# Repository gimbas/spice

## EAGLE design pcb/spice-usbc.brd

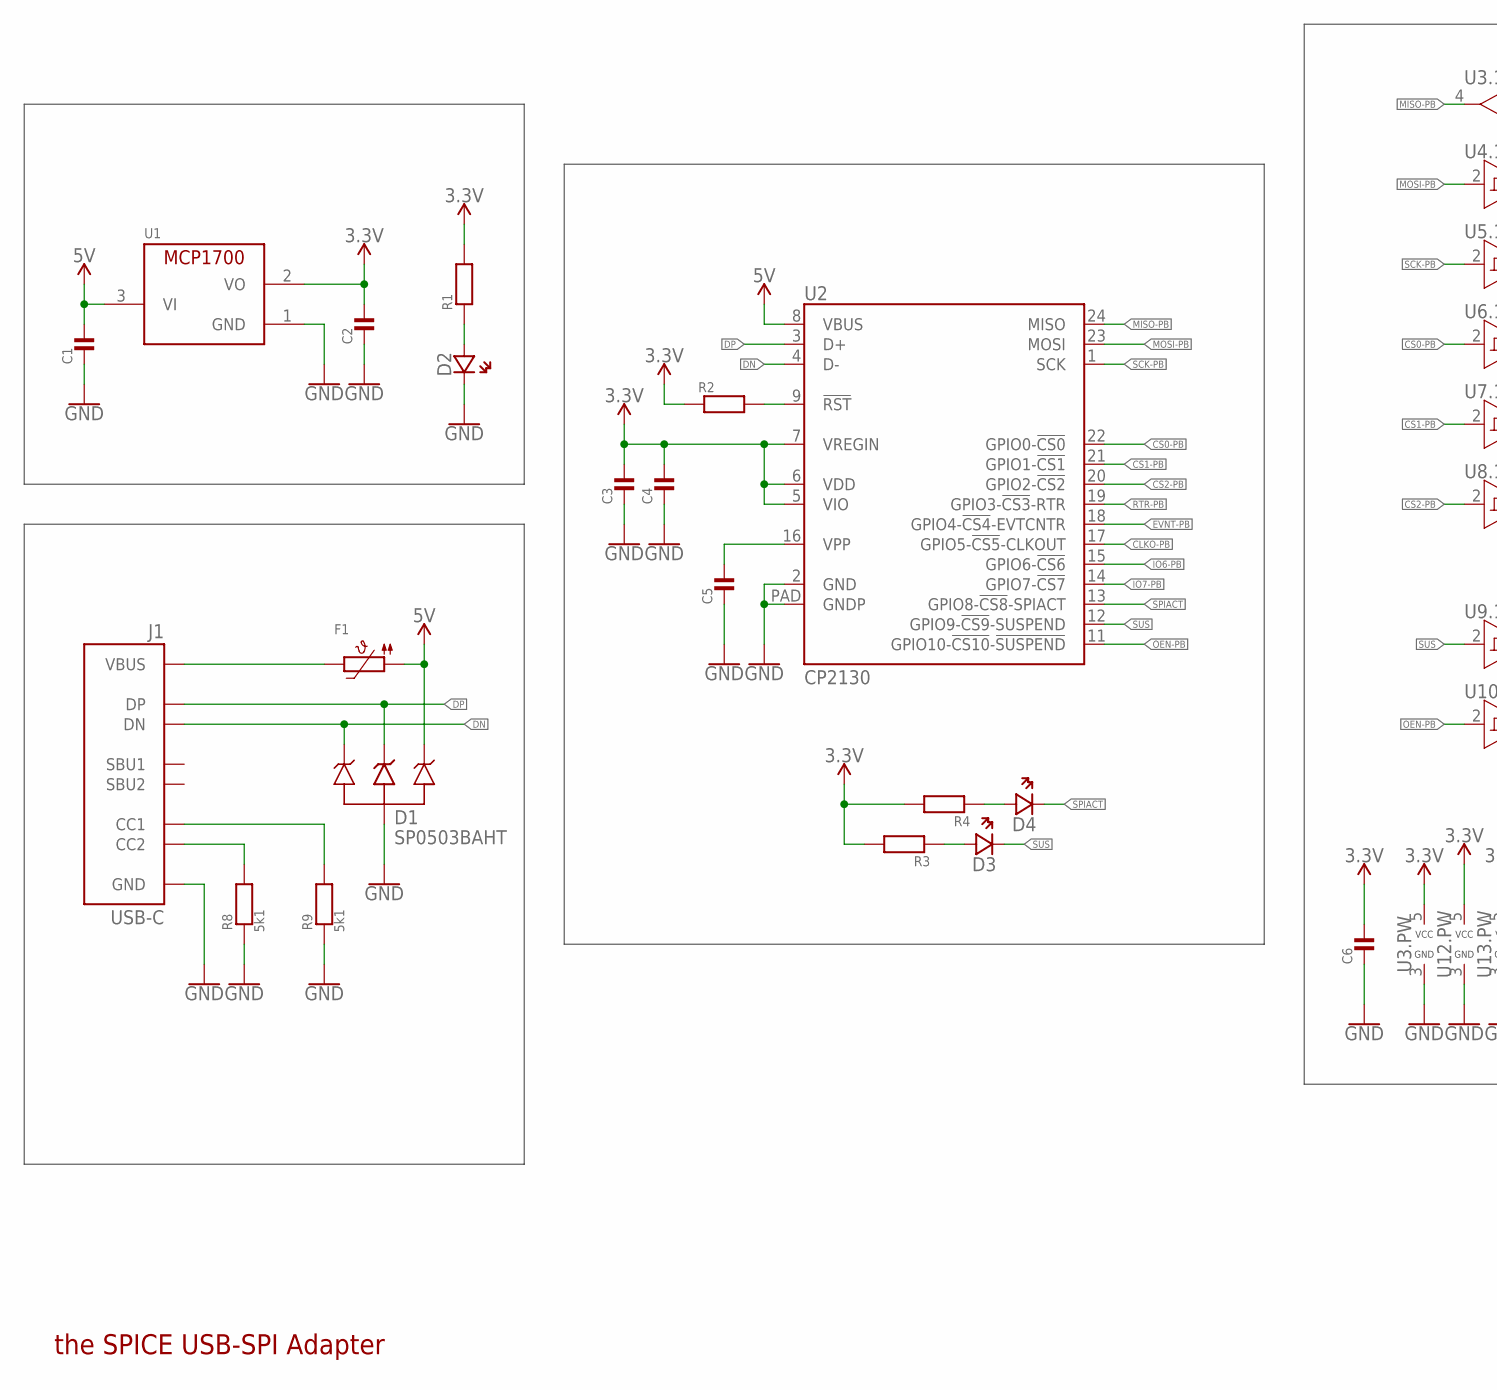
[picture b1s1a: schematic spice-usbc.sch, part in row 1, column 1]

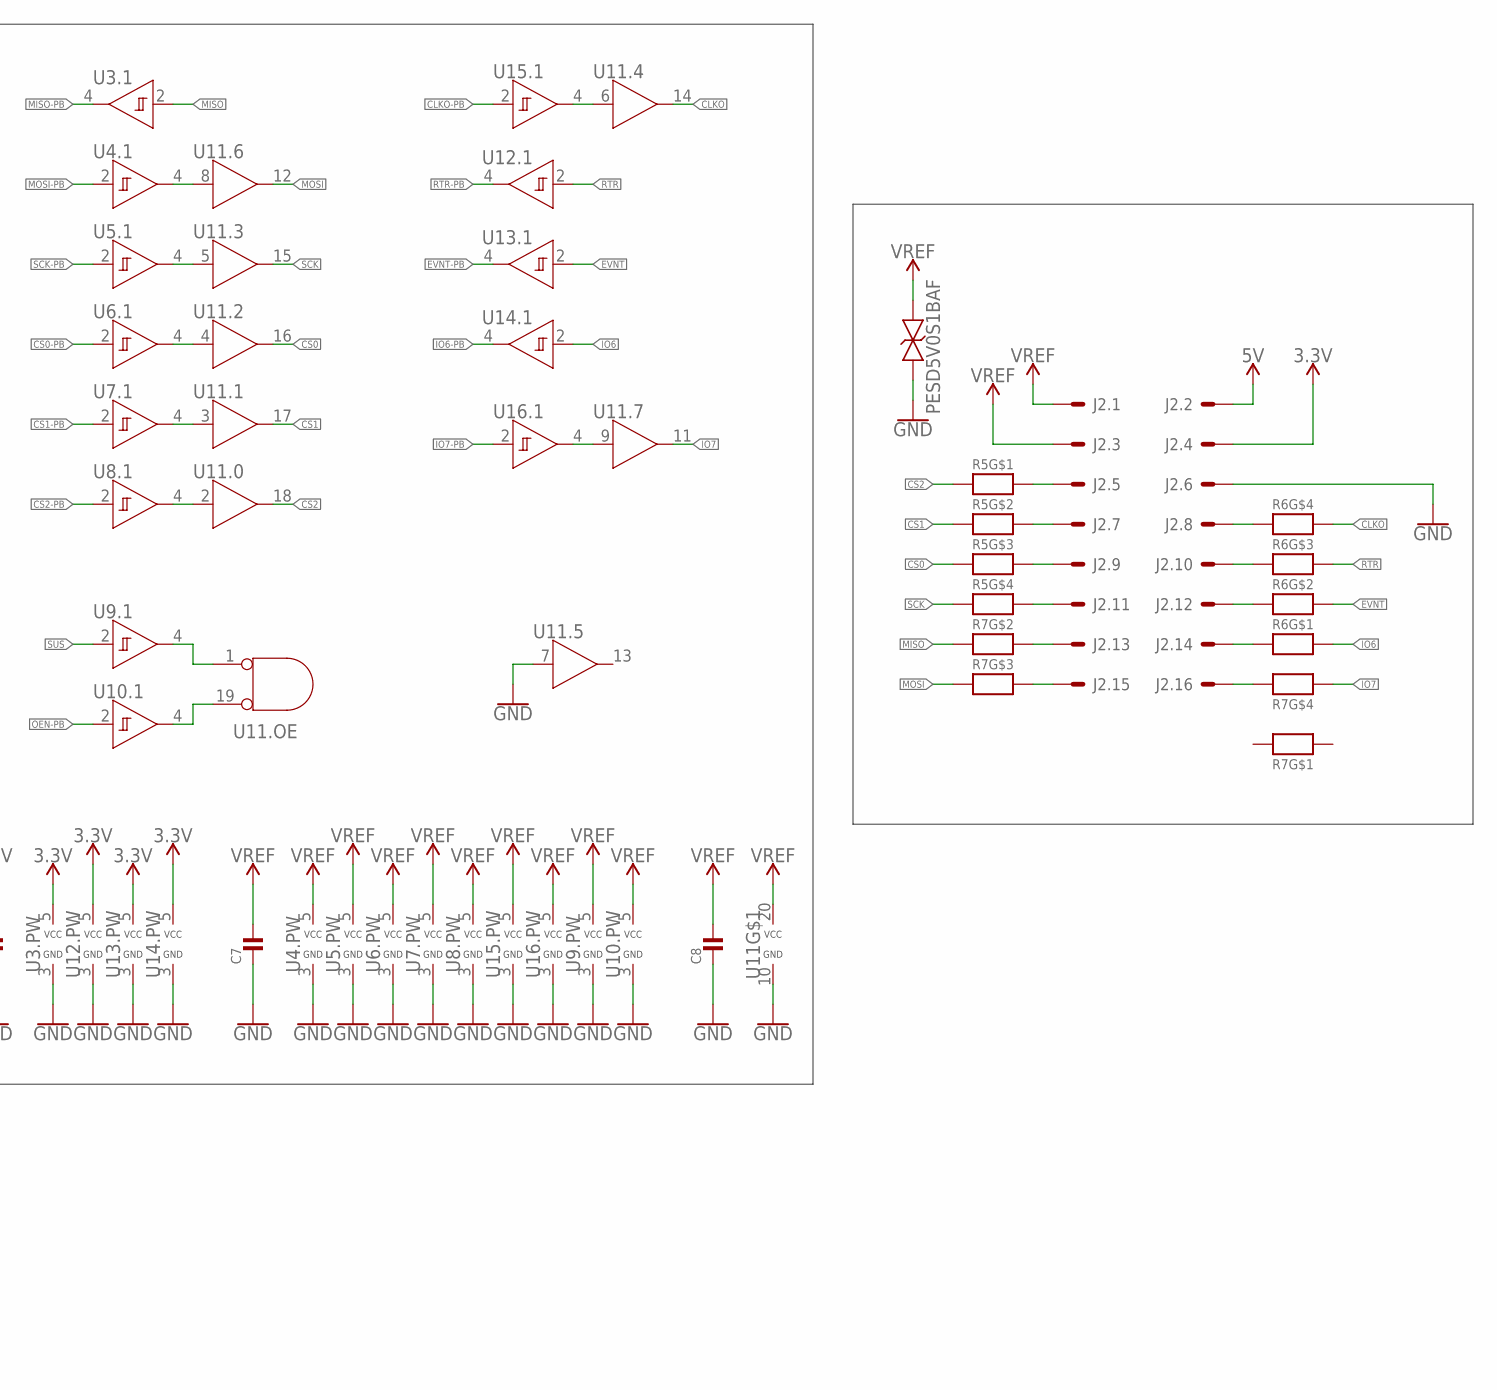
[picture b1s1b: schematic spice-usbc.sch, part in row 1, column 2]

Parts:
C1, C2, C3, C4, C5, C6, C7, C8: MLCC0603; 0603_WAVE
D1: SP0503BAHT; SOT143
D2, D3, D4: LED0603; CHIPLED_0603
D5: PESD5V0S1BAF; SOD323
F1: PTC1210
J1: USB-C
J2: 2X8; 2X8_2.54
R1, R2, R3, R4: RESISTOR0603; 0603_WAVE
R5, R6, R7: RESISTOR_4PACK; RESPACK_4X0603
R8, R9: 5k1; 0603_WAVE
U1: MCP1700T-3302TT; SOT-23
U2: CP2130; QFN24
U3, U4, U5, U6, U7, U8, U9, U10, U12, U13, U14, U15, U16: 74LVC1G17; SC70-5
U11: 74HC541; TSSOP20

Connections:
3.3V: C2.P$1, C3.P$1, C4.P$1, C6.P$1, J2.4, R1.P$2, R2.P$1, R3.P$2, R4.P$2, U1.2 (VO), U2.5 (VIO), U2.6 (VDD), U2.7 (VREGIN), U3.5 (VCC), U12.5 (VCC), U13.5 (VCC), U14.5 (VCC)
5V: C1.P$1, D1.4, F1.P$1 (1), J2.2, U1.3 (VI), U2.8 (VBUS)
CLKO: R6.5 (2), U11.14 (Y)
CLKO-PB: U2.17 (GPIO5-!CS5!-CLKOUT), U15.2 (A)
CS0: R5.3 (1), U11.16 (Y)
CS0-PB: U2.22 (GPIO0-!CS0), U6.2 (A)
CS1: R5.2 (1), U11.17 (Y)
CS1-PB: U2.21 (GPIO1-!CS1), U7.2 (A)
CS2: R5.1, U11.18 (Y)
CS2-PB: U2.20 (GPIO2-!CS2), U8.2 (A)
DN: D1.2, J1.A7 (DN), J1.B7 (DN), U2.4 (D-)
DP: D1.3, J1.A6 (DP), J1.B6 (DP), U2.3 (D+)
EVNT: R6.7 (2), U13.2 (A)
EVNT-PB: U2.18 (GPIO4-!CS4!-EVTCNTR), U13.4 (Y)
GND: C1.P$2, C2.P$2, C3.P$2, C4.P$2, C5.P$2, C6.P$2, C7.P$2, C8.P$2, D1.1, D2.C (CA), D5.P$2, J1.A1_B12 (GND), J1.B1_A12 (GND), J1.SHIELD0 (GND), J1.SHIELD1 (GND), J1.SHIELD2 (GND), J1.SHIELD3 (GND), J2.6, R8.P$1, R9.P$1, U1.1 (GND), U2.2 (GND), U2.PAD (GNDP), U3.3 (GND), U4.3 (GND), U5.3 (GND), U6.3 (GND), U7.3 (GND), U8.3 (GND), U9.3 (GND), U10.3 (GND), U11.7 (A), U11.10 (GND), U12.3 (GND), U13.3 (GND), U14.3 (GND), U15.3 (GND), U16.3 (GND)
IO6: R6.8 (2), U14.2 (A)
IO6-PB: U2.15 (GPIO6-!CS6), U14.4 (Y)
IO7: R7.4 (1), U11.11 (Y)
IO7-PB: U2.14 (GPIO7-!CS7), U16.2 (A)
MISO: R7.2 (1), U3.2 (A)
MISO-PB: U2.24 (MISO), U3.4 (Y)
MOSI: R7.3 (1), U11.12 (Y)
MOSI-PB: U2.23 (MOSI), U4.2 (A)
unnamed: U11.6 (A), U15.4 (Y)
unnamed: D3.A (AN), R3.P$1
unnamed: D4.A (AN), R4.P$1
unnamed: R2.P$2, U2.9 (!RST)
unnamed: U5.4 (Y), U11.5 (A)
unnamed: J2.13, R7.7 (2)
unnamed: U4.4 (Y), U11.8 (A)
unnamed: C5.P$1, U2.16 (VPP)
unnamed: D2.A (AN), R1.P$1
unnamed: U6.4 (Y), U11.4 (A)
unnamed: U7.4 (Y), U11.3 (A)
unnamed: U8.4 (Y), U11.2 (A)
unnamed: F1.P$2 (2), J1.A4_B9 (VBUS), J1.B4_A9 (VBUS)
unnamed: U11.9 (A), U16.4 (Y)
unnamed: J1.B5 (CC2), R8.P$2
unnamed: J2.15, R7.6 (2)
unnamed: J2.5, R5.8 (2)
unnamed: J2.7, R5.7 (2)
unnamed: J2.9, R5.6 (2)
unnamed: J2.11, R5.5 (2)
unnamed: J2.8, R6.4 (1)
unnamed: J2.10, R6.3 (1)
unnamed: J2.12, R6.2 (1)
unnamed: J2.14, R6.1
unnamed: J2.16, R7.5 (2)
unnamed: J1.A5 (CC1), R9.P$2
OE1: U9.4 (Y), U11.1 (A)
OE2: U10.4 (Y), U11.19 (B)
OEN-PB: U2.11 (GPIO10-!CS10!-!SUSPEND), U10.2 (A)
RTR: R6.6 (2), U12.2 (A)
RTR-PB: U2.19 (GPIO3-!CS3!-RTR), U12.4 (Y)
SCK: R5.4 (1), U11.15 (Y)
SCK-PB: U2.1 (SCK), U5.2 (A)
SPIACT: D4.C (CA), U2.13 (GPIO8-!CS8!-SPIACT)
SUS: D3.C (CA), U2.12 (GPIO9-!CS9!-SUSPEND), U9.2 (A)
VREF: C7.P$1, C8.P$1, D5.P$1, J2.1, J2.3, U4.5 (VCC), U5.5 (VCC), U6.5 (VCC), U7.5 (VCC), U8.5 (VCC), U9.5 (VCC), U10.5 (VCC), U11.20 (VCC), U15.5 (VCC), U16.5 (VCC)

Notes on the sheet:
the SPICE USB-SPI Adapter

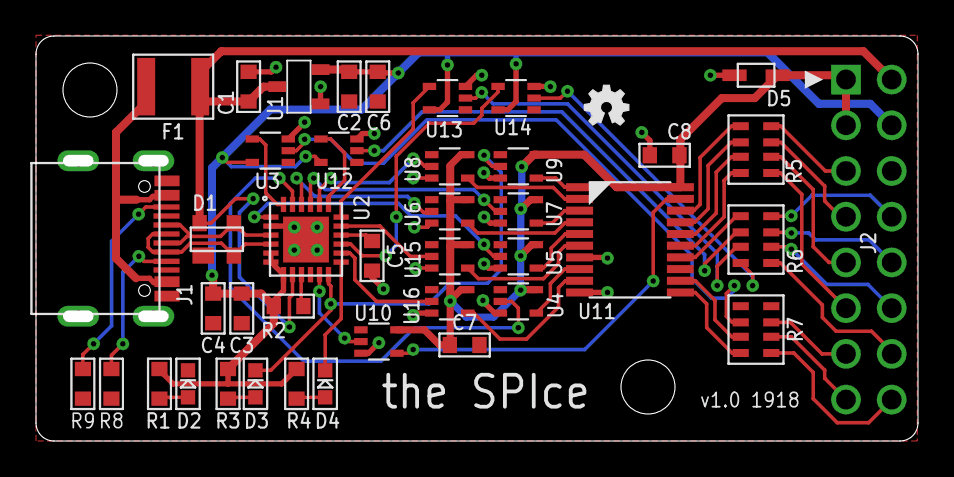
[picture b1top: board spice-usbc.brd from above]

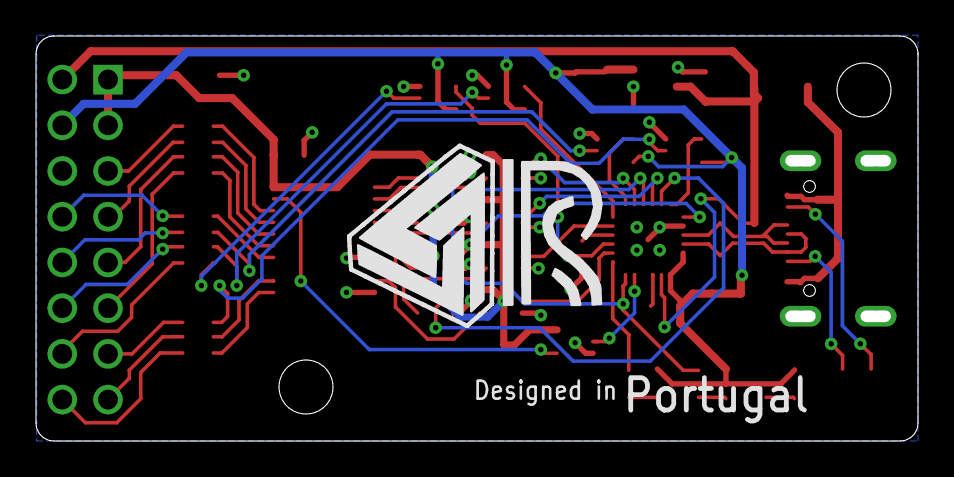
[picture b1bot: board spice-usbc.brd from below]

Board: 2 copper layers, 48.3 x 21.9 mm, 44 parts (2 on the bottom side), 59 nets.

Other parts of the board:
U$1: DESIGNEDINPT
U$2: OSHW-LOGO-MINI
U$4: RAFAEL_SILVA_10MM_ALT

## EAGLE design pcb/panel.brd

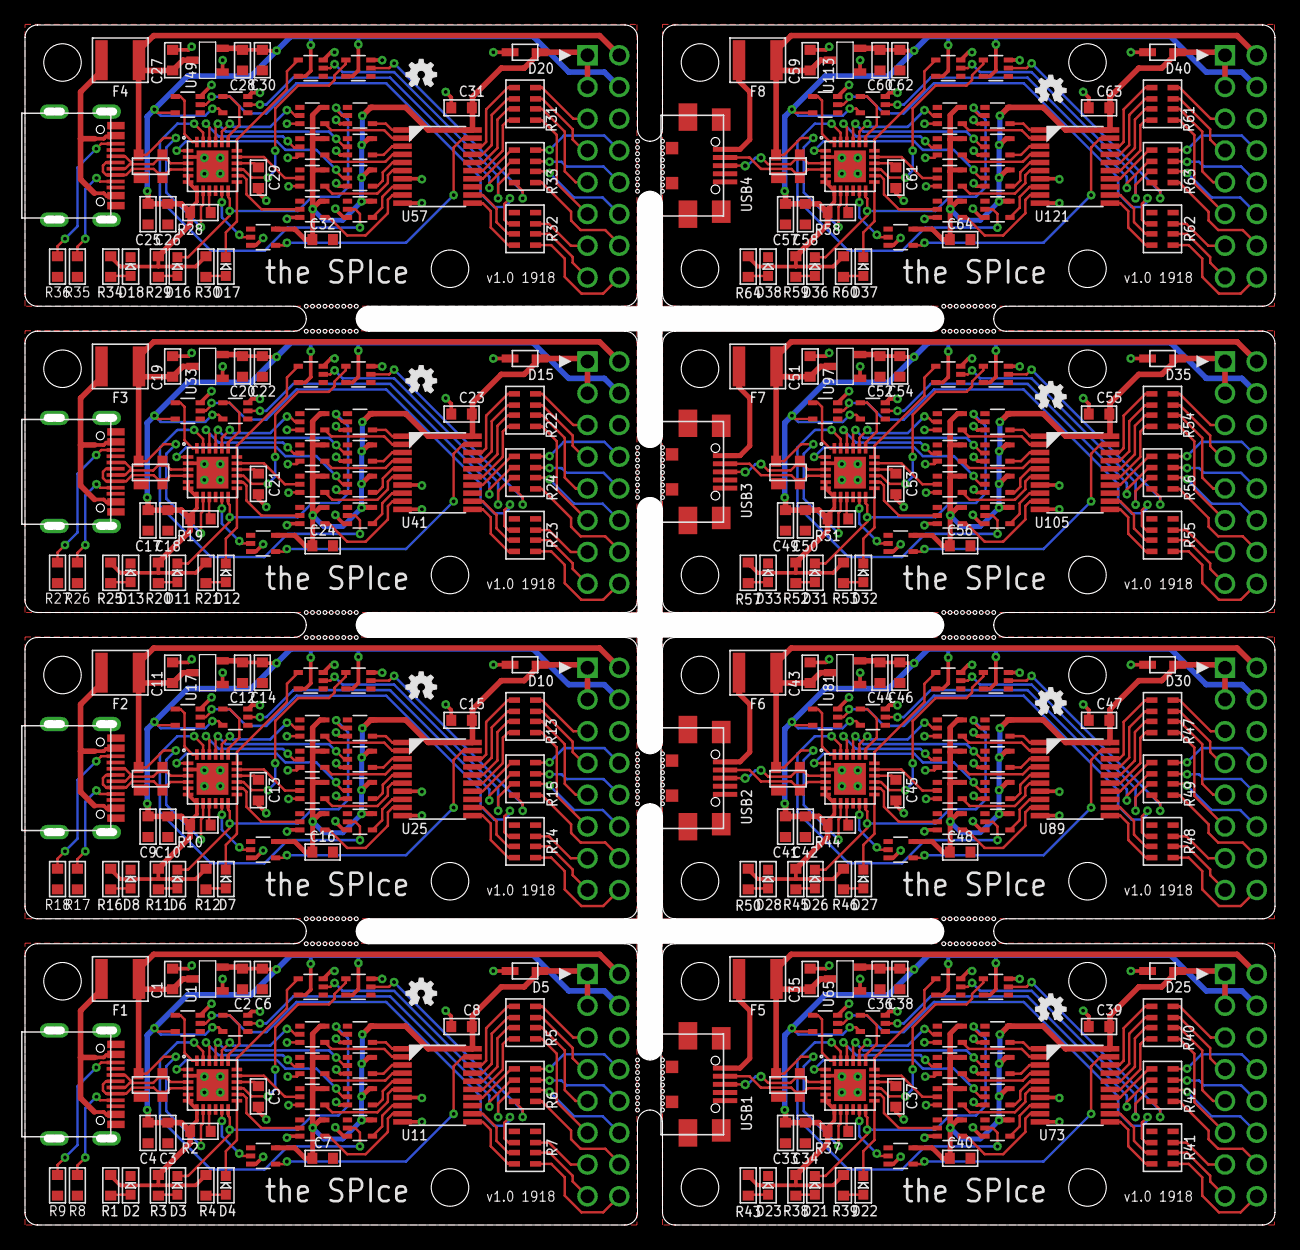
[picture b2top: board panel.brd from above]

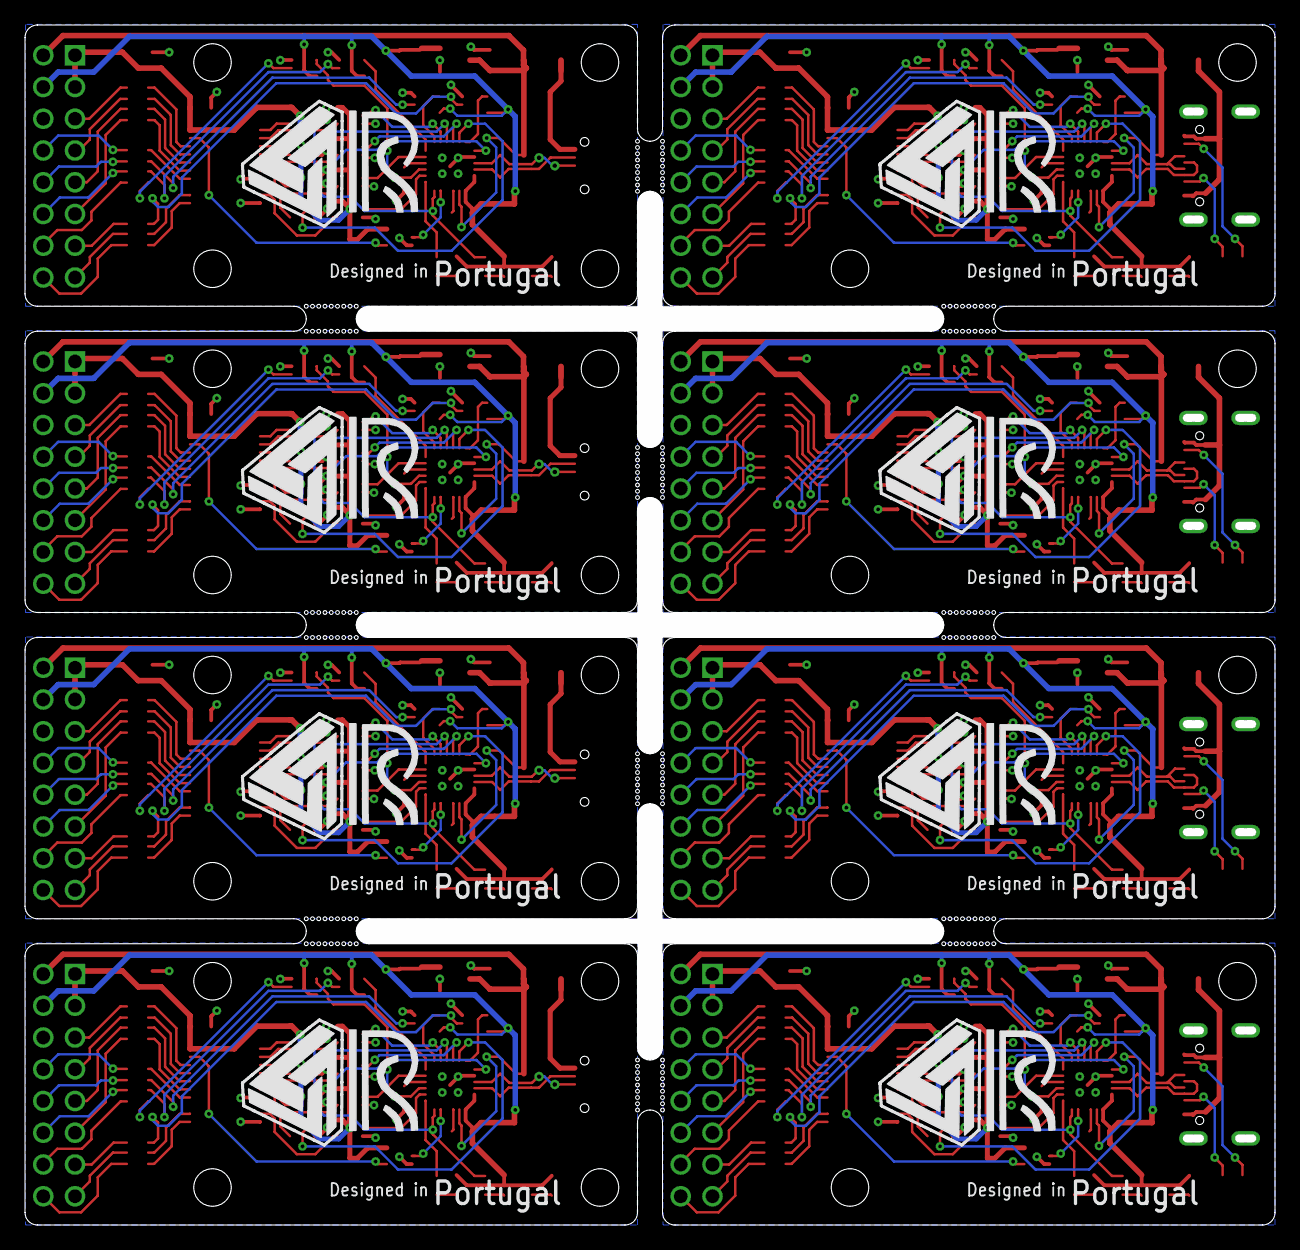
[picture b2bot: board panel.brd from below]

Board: 2 copper layers, 98.0 x 94.0 mm, 344 parts (16 on the bottom side), 464 nets.

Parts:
C1, C2, C3, C4, C5, C6, C7, C8, C9, C10, C11, C12, C13, C14, C15, C16, C17, C18, C19, C20, C21, C22, C23, C24, C25, C26, C27, C28, C29, C30, C31, C32, C33, C34, C35, C36, C37, C38, C39, C40, C41, C42, C43, C44, C45, C46, C47, C48, C49, C50, C51, C52, C53, C54, C55, C56, C57, C58, C59, C60, C61, C62, C63, C64: 0603_WAVE
D1, D9, D14, D19, D24, D29, D34, D39: SP0503BAHT; SOT143
D2, D3, D4, D6, D7, D8, D11, D12, D13, D16, D17, D18, D21, D22, D23, D26, D27, D28, D31, D32, D33, D36, D37, D38: LED0603; CHIPLED_0603
D5, D10, D15, D20, D25, D30, D35, D40: PESD5V0S1BAF; SOD323
F1, F2, F3, F4, F5, F6, F7, F8: PTC1210
J1, J4, J6, J8: USB-C
J2, J3, J5, J7, J9, J10, J11, J12: 2X8; 2X8_2.54
R1, R2, R3, R4, R10, R11, R12, R16, R19, R20, R21, R25, R28, R29, R30, R34, R37, R38, R39, R43, R44, R45, R46, R50, R51, R52, R53, R57, R58, R59, R60, R64: 0603_WAVE
R5, R6, R7, R13, R14, R15, R22, R23, R24, R31, R32, R33, R40, R41, R42, R47, R48, R49, R54, R55, R56, R61, R62, R63: RESPACK_4X0603
R8, R9, R17, R18, R26, R27, R35, R36: 5k1; 0603_WAVE
U1, U17, U33, U49, U65, U81, U97, U113: MCP1700T-3302TT; SOT-23
U2, U18, U34, U50, U66, U82, U98, U114: CP2130; QFN24
U3, U4, U5, U6, U7, U8, U9, U10, U12, U13, U14, U15, U16, U19, U20, U21, U22, U23, U24, U26, U27, U28, U29, U30, U31, U32, U35, U36, U37, U38, U39, U40, U42, U43, U44, U45, U46, U47, U48, U51, U52, U53, U54, U55, U56, U58, U59, U60, U61, U62, U63, U64, U67, U68, U69, U70, U71, U72, U74, U75, U76, U77, U78, U79, U80, U83, U84, U85, U86, U87, U88, U90, U91, U92, U93, U94, U95, U96, U99, U100, U101, U102, U103, U104, U106, U107, U108, U109, U110, U111, U112, U115, U116, U117, U118, U119, U120, U122, U123, U124, U125, U126, U127, U128: 74LVC1G17; SC70-5
U11, U25, U41, U57, U73, U89, U105, U121: 74HC541; TSSOP20
U$1, U$3, U$7, U$10, U$13, U$16, U$19, U$22: DESIGNEDINPT
U$2, U$5, U$8, U$11, U$14, U$17, U$20, U$23: OSHW-LOGO-MINI
U$4, U$6, U$9, U$12, U$15, U$18, U$21, U$24: RAFAEL_SILVA_10MM_ALT
USB1, USB2, USB3, USB4: USB_MICRO-MICRO-B-SMT; USB-MICRO-SMD

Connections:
3.3V: C2.P$1, C3.P$1, C4.P$1, C6.P$1, J2.4, R1.P$2, R2.P$1, R3.P$2, R4.P$2, U1.2, U2.5, U2.6, U2.7, U3.5, U12.5, U13.5, U14.5
3.3V1: C9.P$1, C10.P$1, C12.P$1, C14.P$1, J3.4, R10.P$1, R11.P$2, R12.P$2, R16.P$2, U17.2, U18.5, U18.6, U18.7, U19.5, U20.5, U21.5, U26.5
3.3V2: C17.P$1, C18.P$1, C20.P$1, C22.P$1, J5.4, R19.P$1, R20.P$2, R21.P$2, R25.P$2, U33.2, U34.5, U34.6, U34.7, U35.5, U36.5, U37.5, U42.5
3.3V3: C25.P$1, C26.P$1, C28.P$1, C30.P$1, J7.4, R28.P$1, R29.P$2, R30.P$2, R34.P$2, U49.2, U50.5, U50.6, U50.7, U51.5, U52.5, U53.5, U58.5
3.3V4: C33.P$1, C34.P$1, C36.P$1, C38.P$1, J9.4, R37.P$1, R38.P$2, R39.P$2, R43.P$2, U65.2, U66.5, U66.6, U66.7, U67.5, U68.5, U69.5, U74.5
3.3V5: C41.P$1, C42.P$1, C44.P$1, C46.P$1, J10.4, R44.P$1, R45.P$2, R46.P$2, R50.P$2, U81.2, U82.5, U82.6, U82.7, U83.5, U84.5, U85.5, U90.5
3.3V6: C49.P$1, C50.P$1, C52.P$1, C54.P$1, J11.4, R51.P$1, R52.P$2, R53.P$2, R57.P$2, U97.2, U98.5, U98.6, U98.7, U99.5, U100.5, U101.5, U106.5
3.3V7: C57.P$1, C58.P$1, C60.P$1, C62.P$1, J12.4, R58.P$1, R59.P$2, R60.P$2, R64.P$2, U113.2, U114.5, U114.6, U114.7, U115.5, U116.5, U117.5, U122.5
5V: C1.P$1, D1.4, F1.P$1, J2.2, U1.3, U2.8
5V1: C11.P$1, D9.4, F2.P$1, J3.2, U17.3, U18.8
5V2: C19.P$1, D14.4, F3.P$1, J5.2, U33.3, U34.8
5V3: C27.P$1, D19.4, F4.P$1, J7.2, U49.3, U50.8
5V4: C35.P$1, D24.4, F5.P$1, J9.2, U65.3, U66.8
5V5: C43.P$1, D29.4, F6.P$1, J10.2, U81.3, U82.8
5V6: C51.P$1, D34.4, F7.P$1, J11.2, U97.3, U98.8
5V7: C59.P$1, D39.4, F8.P$1, J12.2, U113.3, U114.8
CLKO: R6.5, U11.14
CLKO1: R15.5, U25.14
CLKO2: R24.5, U41.14
CLKO3: R33.5, U57.14
CLKO4: R42.5, U73.14
CLKO5: R49.5, U89.14
CLKO6: R56.5, U105.14
CLKO7: R63.5, U121.14
CLKO-PB: U2.17, U15.2
CLKO-PB1: U18.17, U32.2
CLKO-PB2: U34.17, U48.2
CLKO-PB3: U50.17, U64.2
CLKO-PB4: U66.17, U80.2
CLKO-PB5: U82.17, U96.2
CLKO-PB6: U98.17, U112.2
CLKO-PB7: U114.17, U128.2
CS0: R5.3, U11.16
CS0-PB: U2.22, U6.2
CS0-PB1: U18.22, U29.2
CS0-PB2: U34.22, U45.2
CS0-PB3: U50.22, U61.2
CS0-PB4: U66.22, U77.2
CS0-PB5: U82.22, U93.2
CS0-PB6: U98.22, U109.2
CS0-PB7: U114.22, U125.2
CS1: R5.2, U11.17
CS1-PB: U2.21, U7.2
CS1-PB1: U18.21, U30.2
CS1-PB2: U34.21, U46.2
CS1-PB3: U50.21, U62.2
CS1-PB4: U66.21, U78.2
CS1-PB5: U82.21, U94.2
CS1-PB6: U98.21, U110.2
CS1-PB7: U114.21, U126.2
CS2: R5.1, U11.18
CS2-PB: U2.20, U8.2
CS2-PB1: U18.20, U31.2
CS2-PB2: U34.20, U47.2
CS2-PB3: U50.20, U63.2
CS2-PB4: U66.20, U79.2
CS2-PB5: U82.20, U95.2
CS2-PB6: U98.20, U111.2
CS2-PB7: U114.20, U127.2
CS3: R13.3, U25.16
CS4: R13.2, U25.17
CS5: R13.1, U25.18
CS6: R22.3, U41.16
CS7: R22.2, U41.17
CS8: R22.1, U41.18
CS9: R31.3, U57.16
CS10: R31.2, U57.17
CS11: R31.1, U57.18
CS12: R40.3, U73.16
CS13: R40.2, U73.17
CS14: R40.1, U73.18
CS15: R47.3, U89.16
CS16: R47.2, U89.17
CS17: R47.1, U89.18
CS18: R54.3, U105.16
CS19: R54.2, U105.17
CS20: R54.1, U105.18
CS21: R61.3, U121.16
CS22: R61.2, U121.17
CS23: R61.1, U121.18
DN: D1.2, J1.A7, J1.B7, U2.4
DN1: D9.2, J4.A7, J4.B7, U18.4
DN2: D14.2, J6.A7, J6.B7, U34.4
DN3: D19.2, J8.A7, J8.B7, U50.4
DN4: D24.2, U66.4, USB1.D-
DN5: D29.2, U82.4, USB2.D-
DN6: D34.2, U98.4, USB3.D-
DN7: D39.2, U114.4, USB4.D-
DP: D1.3, J1.A6, J1.B6, U2.3
DP1: D9.3, J4.A6, J4.B6, U18.3
DP2: D14.3, J6.A6, J6.B6, U34.3
DP3: D19.3, J8.A6, J8.B6, U50.3
DP4: D24.3, U66.3, USB1.D+
DP5: D29.3, U82.3, USB2.D+
DP6: D34.3, U98.3, USB3.D+
DP7: D39.3, U114.3, USB4.D+
EVNT: R6.7, U13.2
EVNT1: R15.7, U20.2
EVNT2: R24.7, U36.2
EVNT3: R33.7, U52.2
EVNT4: R42.7, U68.2
EVNT5: R49.7, U84.2
EVNT6: R56.7, U100.2
EVNT7: R63.7, U116.2
EVNT-PB: U2.18, U13.4
EVNT-PB1: U18.18, U20.4
EVNT-PB2: U34.18, U36.4
EVNT-PB3: U50.18, U52.4
EVNT-PB4: U66.18, U68.4
EVNT-PB5: U82.18, U84.4
EVNT-PB6: U98.18, U100.4
EVNT-PB7: U114.18, U116.4
GND: C1.P$2, C2.P$2, C3.P$2, C4.P$2, C5.P$2, C6.P$2, C7.P$2, C8.P$2, D1.1, D2.C, D5.P$2, J1.A1_B12, J1.B1_A12, J1.SHIELD0, J1.SHIELD1, J1.SHIELD2, J1.SHIELD3, J2.6, R8.P$1, R9.P$1, U1.1, U2.2, U2.PAD, U3.3, U4.3, U5.3, U6.3, U7.3, U8.3, U9.3, U10.3, U11.7, U11.10, U12.3, U13.3, U14.3, U15.3, U16.3
GND1: C9.P$2, C10.P$2, C11.P$2, C12.P$2, C13.P$2, C14.P$2, C15.P$2, C16.P$2, D8.C, D9.1, D10.P$2, J3.6, J4.A1_B12, J4.B1_A12, J4.SHIELD0, J4.SHIELD1, J4.SHIELD2, J4.SHIELD3, R17.P$1, R18.P$1, U17.1, U18.2, U18.PAD, U19.3, U20.3, U21.3, U22.3, U23.3, U24.3, U25.7, U25.10, U26.3, U27.3, U28.3, U29.3, U30.3, U31.3, U32.3
GND2: C17.P$2, C18.P$2, C19.P$2, C20.P$2, C21.P$2, C22.P$2, C23.P$2, C24.P$2, D13.C, D14.1, D15.P$2, J5.6, J6.A1_B12, J6.B1_A12, J6.SHIELD0, J6.SHIELD1, J6.SHIELD2, J6.SHIELD3, R26.P$1, R27.P$1, U33.1, U34.2, U34.PAD, U35.3, U36.3, U37.3, U38.3, U39.3, U40.3, U41.7, U41.10, U42.3, U43.3, U44.3, U45.3, U46.3, U47.3, U48.3
GND3: C25.P$2, C26.P$2, C27.P$2, C28.P$2, C29.P$2, C30.P$2, C31.P$2, C32.P$2, D18.C, D19.1, D20.P$2, J7.6, J8.A1_B12, J8.B1_A12, J8.SHIELD0, J8.SHIELD1, J8.SHIELD2, J8.SHIELD3, R35.P$1, R36.P$1, U49.1, U50.2, U50.PAD, U51.3, U52.3, U53.3, U54.3, U55.3, U56.3, U57.7, U57.10, U58.3, U59.3, U60.3, U61.3, U62.3, U63.3, U64.3
GND4: C33.P$2, C34.P$2, C35.P$2, C36.P$2, C37.P$2, C38.P$2, C39.P$2, C40.P$2, D23.C, D24.1, D25.P$2, J9.6, U65.1, U66.2, U66.PAD, U67.3, U68.3, U69.3, U70.3, U71.3, U72.3, U73.7, U73.10, U74.3, U75.3, U76.3, U77.3, U78.3, U79.3, U80.3, USB1.GND, USB1.SHIELD1, USB1.SHIELD2, USB1.SHIELD3, USB1.SHIELD4, USB1.SHIELD5, USB1.SHIELD6
GND5: C41.P$2, C42.P$2, C43.P$2, C44.P$2, C45.P$2, C46.P$2, C47.P$2, C48.P$2, D28.C, D29.1, D30.P$2, J10.6, U81.1, U82.2, U82.PAD, U83.3, U84.3, U85.3, U86.3, U87.3, U88.3, U89.7, U89.10, U90.3, U91.3, U92.3, U93.3, U94.3, U95.3, U96.3, USB2.GND, USB2.SHIELD1, USB2.SHIELD2, USB2.SHIELD3, USB2.SHIELD4, USB2.SHIELD5, USB2.SHIELD6
GND6: C49.P$2, C50.P$2, C51.P$2, C52.P$2, C53.P$2, C54.P$2, C55.P$2, C56.P$2, D33.C, D34.1, D35.P$2, J11.6, U97.1, U98.2, U98.PAD, U99.3, U100.3, U101.3, U102.3, U103.3, U104.3, U105.7, U105.10, U106.3, U107.3, U108.3, U109.3, U110.3, U111.3, U112.3, USB3.GND, USB3.SHIELD1, USB3.SHIELD2, USB3.SHIELD3, USB3.SHIELD4, USB3.SHIELD5, USB3.SHIELD6
GND7: C57.P$2, C58.P$2, C59.P$2, C60.P$2, C61.P$2, C62.P$2, C63.P$2, C64.P$2, D38.C, D39.1, D40.P$2, J12.6, U113.1, U114.2, U114.PAD, U115.3, U116.3, U117.3, U118.3, U119.3, U120.3, U121.7, U121.10, U122.3, U123.3, U124.3, U125.3, U126.3, U127.3, U128.3, USB4.GND, USB4.SHIELD1, USB4.SHIELD2, USB4.SHIELD3, USB4.SHIELD4, USB4.SHIELD5, USB4.SHIELD6
IO1: R14.4, U25.11
IO2: R15.8, U21.2
IO3: R23.4, U41.11
IO4: R24.8, U37.2
IO5: R32.4, U57.11
IO6: R6.8, U14.2
IO6-PB: U2.15, U14.4
IO6-PB1: U18.15, U21.4
IO6-PB2: U34.15, U37.4
IO6-PB3: U50.15, U53.4
IO6-PB4: U66.15, U69.4
IO6-PB5: U82.15, U85.4
IO6-PB6: U98.15, U101.4
IO6-PB7: U114.15, U117.4
IO7: R7.4, U11.11
IO7-PB: U2.14, U16.2
IO7-PB1: U18.14, U22.2
IO7-PB2: U34.14, U38.2
IO7-PB3: U50.14, U54.2
IO7-PB4: U66.14, U70.2
IO7-PB5: U82.14, U86.2
IO7-PB6: U98.14, U102.2
IO7-PB7: U114.14, U118.2
IO8: R33.8, U53.2
IO9: R41.4, U73.11
IO10: R42.8, U69.2
IO11: R48.4, U89.11
IO12: R49.8, U85.2
IO13: R55.4, U105.11
IO14: R56.8, U101.2
IO15: R62.4, U121.11
IO16: R63.8, U117.2
MISO: R7.2, U3.2
MISO1: R14.2, U26.2
MISO2: R23.2, U42.2
MISO3: R32.2, U58.2
MISO4: R41.2, U74.2
MISO5: R48.2, U90.2
MISO6: R55.2, U106.2
MISO7: R62.2, U122.2
MISO-PB: U2.24, U3.4
MISO-PB1: U18.24, U26.4
MISO-PB2: U34.24, U42.4
MISO-PB3: U50.24, U58.4
MISO-PB4: U66.24, U74.4
MISO-PB5: U82.24, U90.4
MISO-PB6: U98.24, U106.4
MISO-PB7: U114.24, U122.4
MOSI: R7.3, U11.12
MOSI1: R14.3, U25.12
MOSI2: R23.3, U41.12
MOSI3: R32.3, U57.12
MOSI4: R41.3, U73.12
MOSI5: R48.3, U89.12
MOSI6: R55.3, U105.12
MOSI7: R62.3, U121.12
MOSI-PB: U2.23, U4.2
MOSI-PB1: U18.23, U27.2
MOSI-PB2: U34.23, U43.2
MOSI-PB3: U50.23, U59.2
MOSI-PB4: U66.23, U75.2
MOSI-PB5: U82.23, U91.2
MOSI-PB6: U98.23, U107.2
MOSI-PB7: U114.23, U123.2
unnamed: U11.6, U15.4
unnamed: D3.A, R3.P$1
unnamed: D4.A, R4.P$1
unnamed: R2.P$2, U2.9
unnamed: U5.4, U11.5
unnamed: J2.13, R7.7
unnamed: U4.4, U11.8
unnamed: C5.P$1, U2.16
unnamed: D2.A, R1.P$1
unnamed: U6.4, U11.4
unnamed: U7.4, U11.3
unnamed: U8.4, U11.2
unnamed: F1.P$2, J1.A4_B9, J1.B4_A9
unnamed: U11.9, U16.4
unnamed: J1.B5, R8.P$2
unnamed: J2.15, R7.6
unnamed: J2.5, R5.8
unnamed: J2.7, R5.7
unnamed: J2.9, R5.6
unnamed: J2.11, R5.5
unnamed: J2.8, R6.4
unnamed: J2.10, R6.3
unnamed: J2.12, R6.2
unnamed: J2.14, R6.1
unnamed: J2.16, R7.5
unnamed: J1.A5, R9.P$2
unnamed: R10.P$2, U18.9
unnamed: C13.P$1, U18.16
unnamed: D6.A, R11.P$1
unnamed: D7.A, R12.P$1
unnamed: D8.A, R16.P$1
unnamed: J3.8, R15.4
unnamed: J3.10, R15.3
unnamed: J3.12, R15.2
unnamed: J3.14, R15.1
unnamed: J3.16, R14.5
unnamed: J3.13, R14.7
unnamed: J3.15, R14.6
unnamed: J3.5, R13.8
unnamed: J3.7, R13.7
unnamed: J3.9, R13.6
unnamed: J3.11, R13.5
unnamed: U22.4, U25.9
unnamed: U25.8, U27.4
unnamed: U25.6, U32.4
unnamed: U25.5, U28.4
unnamed: U25.4, U29.4
unnamed: U25.3, U30.4
unnamed: U25.2, U31.4
unnamed: F2.P$2, J4.A4_B9, J4.B4_A9
unnamed: J4.B5, R17.P$2
unnamed: J4.A5, R18.P$2
unnamed: R19.P$2, U34.9
unnamed: C21.P$1, U34.16
unnamed: D11.A, R20.P$1
unnamed: D12.A, R21.P$1
unnamed: D13.A, R25.P$1
unnamed: J5.8, R24.4
unnamed: J5.10, R24.3
unnamed: J5.12, R24.2
unnamed: J5.14, R24.1
unnamed: J5.16, R23.5
unnamed: J5.13, R23.7
unnamed: J5.15, R23.6
unnamed: J5.5, R22.8
unnamed: J5.7, R22.7
unnamed: J5.9, R22.6
unnamed: J5.11, R22.5
unnamed: U38.4, U41.9
unnamed: U41.8, U43.4
unnamed: U41.6, U48.4
unnamed: U41.5, U44.4
unnamed: U41.4, U45.4
unnamed: U41.3, U46.4
unnamed: U41.2, U47.4
unnamed: F3.P$2, J6.A4_B9, J6.B4_A9
unnamed: J6.B5, R26.P$2
unnamed: J6.A5, R27.P$2
unnamed: R28.P$2, U50.9
unnamed: C29.P$1, U50.16
unnamed: D16.A, R29.P$1
unnamed: D17.A, R30.P$1
unnamed: D18.A, R34.P$1
unnamed: J7.8, R33.4
unnamed: J7.10, R33.3
unnamed: J7.12, R33.2
unnamed: J7.14, R33.1
unnamed: J7.16, R32.5
unnamed: J7.13, R32.7
unnamed: J7.15, R32.6
unnamed: J7.5, R31.8
unnamed: J7.7, R31.7
unnamed: J7.9, R31.6
unnamed: J7.11, R31.5
unnamed: U54.4, U57.9
unnamed: U57.8, U59.4
unnamed: U57.6, U64.4
unnamed: U57.5, U60.4
unnamed: U57.4, U61.4
unnamed: U57.3, U62.4
unnamed: U57.2, U63.4
unnamed: F4.P$2, J8.A4_B9, J8.B4_A9
unnamed: J8.B5, R35.P$2
unnamed: J8.A5, R36.P$2
unnamed: R37.P$2, U66.9
unnamed: C37.P$1, U66.16
unnamed: D21.A, R38.P$1
unnamed: D22.A, R39.P$1
unnamed: D23.A, R43.P$1
unnamed: J9.8, R42.4
unnamed: J9.10, R42.3
unnamed: J9.12, R42.2
unnamed: J9.14, R42.1
unnamed: J9.16, R41.5
unnamed: J9.13, R41.7
unnamed: J9.15, R41.6
unnamed: J9.5, R40.8
unnamed: J9.7, R40.7
unnamed: J9.9, R40.6
unnamed: J9.11, R40.5
unnamed: U70.4, U73.9
unnamed: U73.8, U75.4
unnamed: U73.6, U80.4
unnamed: U73.5, U76.4
unnamed: U73.4, U77.4
unnamed: U73.3, U78.4
unnamed: U73.2, U79.4
unnamed: F5.P$2, USB1.VBUS
unnamed: R44.P$2, U82.9
unnamed: C45.P$1, U82.16
unnamed: D26.A, R45.P$1
unnamed: D27.A, R46.P$1
unnamed: D28.A, R50.P$1
unnamed: J10.8, R49.4
unnamed: J10.10, R49.3
unnamed: J10.12, R49.2
unnamed: J10.14, R49.1
unnamed: J10.16, R48.5
unnamed: J10.13, R48.7
unnamed: J10.15, R48.6
unnamed: J10.5, R47.8
unnamed: J10.7, R47.7
unnamed: J10.9, R47.6
unnamed: J10.11, R47.5
unnamed: U86.4, U89.9
unnamed: U89.8, U91.4
unnamed: U89.6, U96.4
unnamed: U89.5, U92.4
unnamed: U89.4, U93.4
unnamed: U89.3, U94.4
unnamed: U89.2, U95.4
unnamed: F6.P$2, USB2.VBUS
unnamed: R51.P$2, U98.9
unnamed: C53.P$1, U98.16
unnamed: D31.A, R52.P$1
unnamed: D32.A, R53.P$1
unnamed: D33.A, R57.P$1
unnamed: J11.8, R56.4
unnamed: J11.10, R56.3
unnamed: J11.12, R56.2
unnamed: J11.14, R56.1
unnamed: J11.16, R55.5
unnamed: J11.13, R55.7
unnamed: J11.15, R55.6
unnamed: J11.5, R54.8
unnamed: J11.7, R54.7
unnamed: J11.9, R54.6
unnamed: J11.11, R54.5
unnamed: U102.4, U105.9
unnamed: U105.8, U107.4
unnamed: U105.6, U112.4
unnamed: U105.5, U108.4
unnamed: U105.4, U109.4
unnamed: U105.3, U110.4
unnamed: U105.2, U111.4
unnamed: F7.P$2, USB3.VBUS
unnamed: R58.P$2, U114.9
unnamed: C61.P$1, U114.16
unnamed: D36.A, R59.P$1
unnamed: D37.A, R60.P$1
unnamed: D38.A, R64.P$1
unnamed: J12.8, R63.4
unnamed: J12.10, R63.3
unnamed: J12.12, R63.2
unnamed: J12.14, R63.1
unnamed: J12.16, R62.5
unnamed: J12.13, R62.7
unnamed: J12.15, R62.6
unnamed: J12.5, R61.8
unnamed: J12.7, R61.7
unnamed: J12.9, R61.6
unnamed: J12.11, R61.5
unnamed: U118.4, U121.9
unnamed: U121.8, U123.4
unnamed: U121.6, U128.4
unnamed: U121.5, U124.4
unnamed: U121.4, U125.4
unnamed: U121.3, U126.4
unnamed: U121.2, U127.4
unnamed: F8.P$2, USB4.VBUS
OE1: U9.4, U11.1
OE2: U10.4, U11.19
OE3: U24.4, U25.19
OE4: U23.4, U25.1
OE5: U40.4, U41.19
OE6: U39.4, U41.1
OE7: U56.4, U57.19
OE8: U55.4, U57.1
OE9: U72.4, U73.19
OE10: U71.4, U73.1
OE11: U88.4, U89.19
OE12: U87.4, U89.1
OE13: U104.4, U105.19
OE14: U103.4, U105.1
OE15: U120.4, U121.19
OE16: U119.4, U121.1
OEN-PB: U2.11, U10.2
OEN-PB1: U18.11, U24.2
OEN-PB2: U34.11, U40.2
OEN-PB3: U50.11, U56.2
OEN-PB4: U66.11, U72.2
OEN-PB5: U82.11, U88.2
OEN-PB6: U98.11, U104.2
OEN-PB7: U114.11, U120.2
RTR: R6.6, U12.2
RTR1: R15.6, U19.2
RTR2: R24.6, U35.2
RTR3: R33.6, U51.2
RTR4: R42.6, U67.2
RTR5: R49.6, U83.2
RTR6: R56.6, U99.2
RTR7: R63.6, U115.2
RTR-PB: U2.19, U12.4
RTR-PB1: U18.19, U19.4
RTR-PB2: U34.19, U35.4
RTR-PB3: U50.19, U51.4
RTR-PB4: U66.19, U67.4
RTR-PB5: U82.19, U83.4
RTR-PB6: U98.19, U99.4
RTR-PB7: U114.19, U115.4
SCK: R5.4, U11.15
SCK1: R13.4, U25.15
SCK2: R22.4, U41.15
SCK3: R31.4, U57.15
SCK4: R40.4, U73.15
SCK5: R47.4, U89.15
SCK6: R54.4, U105.15
SCK7: R61.4, U121.15
SCK-PB: U2.1, U5.2
SCK-PB1: U18.1, U28.2
SCK-PB2: U34.1, U44.2
SCK-PB3: U50.1, U60.2
SCK-PB4: U66.1, U76.2
SCK-PB5: U82.1, U92.2
SCK-PB6: U98.1, U108.2
SCK-PB7: U114.1, U124.2
SPIACT: D4.C, U2.13
SPIACT1: D7.C, U18.13
SPIACT2: D12.C, U34.13
SPIACT3: D17.C, U50.13
SPIACT4: D22.C, U66.13
SPIACT5: D27.C, U82.13
SPIACT6: D32.C, U98.13
SPIACT7: D37.C, U114.13
SUS: D3.C, U2.12, U9.2
SUS1: D6.C, U18.12, U23.2
SUS2: D11.C, U34.12, U39.2
SUS3: D16.C, U50.12, U55.2
SUS4: D21.C, U66.12, U71.2
SUS5: D26.C, U82.12, U87.2
SUS6: D31.C, U98.12, U103.2
SUS7: D36.C, U114.12, U119.2
VREF: C7.P$1, C8.P$1, D5.P$1, J2.1, J2.3, U4.5, U5.5, U6.5, U7.5, U8.5, U9.5, U10.5, U11.20, U15.5, U16.5
VREF1: C15.P$1, C16.P$1, D10.P$1, J3.1, J3.3, U22.5, U23.5, U24.5, U25.20, U27.5, U28.5, U29.5, U30.5, U31.5, U32.5
VREF2: C23.P$1, C24.P$1, D15.P$1, J5.1, J5.3, U38.5, U39.5, U40.5, U41.20, U43.5, U44.5, U45.5, U46.5, U47.5, U48.5
VREF3: C31.P$1, C32.P$1, D20.P$1, J7.1, J7.3, U54.5, U55.5, U56.5, U57.20, U59.5, U60.5, U61.5, U62.5, U63.5, U64.5
VREF4: C39.P$1, C40.P$1, D25.P$1, J9.1, J9.3, U70.5, U71.5, U72.5, U73.20, U75.5, U76.5, U77.5, U78.5, U79.5, U80.5
VREF5: C47.P$1, C48.P$1, D30.P$1, J10.1, J10.3, U86.5, U87.5, U88.5, U89.20, U91.5, U92.5, U93.5, U94.5, U95.5, U96.5
VREF6: C55.P$1, C56.P$1, D35.P$1, J11.1, J11.3, U102.5, U103.5, U104.5, U105.20, U107.5, U108.5, U109.5, U110.5, U111.5, U112.5
VREF7: C63.P$1, C64.P$1, D40.P$1, J12.1, J12.3, U118.5, U119.5, U120.5, U121.20, U123.5, U124.5, U125.5, U126.5, U127.5, U128.5

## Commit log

2019-04-28 root commit
2019-04-29 finished pcbs, generated gerbers
2019-05-07 Reorganized
2019-05-16 fixed usb c connector
2019-05-16 fixed usb connector
2019-05-17 Add USB C CC lines pull down
2019-05-31 panelize
2019-09-19 sync

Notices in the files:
parts and their libraries:
Utility: Released under the Creative Commons
Utility: https://creativecommons.org/licenses/by-sa/4.0
